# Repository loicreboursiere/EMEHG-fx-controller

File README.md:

# EMEHG-fx-controller

This repository gathers all elements needed to build and run EMEHG-fx-controller.
This device contains a 4x7 rotary encoders matrix with push option.
The encoders matrix aims at controlling hexaphonic audio effects parameters through MIDI CC messages.
 As it sends out MIDI commands, this controller can be use for any kind of control operation.
 This project is a part of the developments made for Loïc Reboursière Phd Thesis : 
    "Organology, genealogy and practice of hexaphonic guitar : from independent string effects to instrumental control of other sounds." 
 
This version is based on a Teensy 3.2. The PCB has been moved to a separate box and Oled display and master rotary encoders has been added.
 
 The folder is organized as follows : 
 ```
 EMEHG-fx-controller.
 └───cad_drawings
 └───code
 └───datasheet
 └───fritzing
 └───img
 └───pcb
 └───Pd
 ```
- cad_drawings : contains a document with drawings of rotaries with the correct spacing.
- code : contains the code to be uploaded on the microcontroller. Depending on the version you're using, the structure of this folder can change (Arduino sketch or Platform IO (through VS) code).
- datasheet : datasheets of used components.
- img : pictures of the different versions of the controller.
- pcb : files for producing pcb
- Pd : test pd patches that receive data from the controller and display them.

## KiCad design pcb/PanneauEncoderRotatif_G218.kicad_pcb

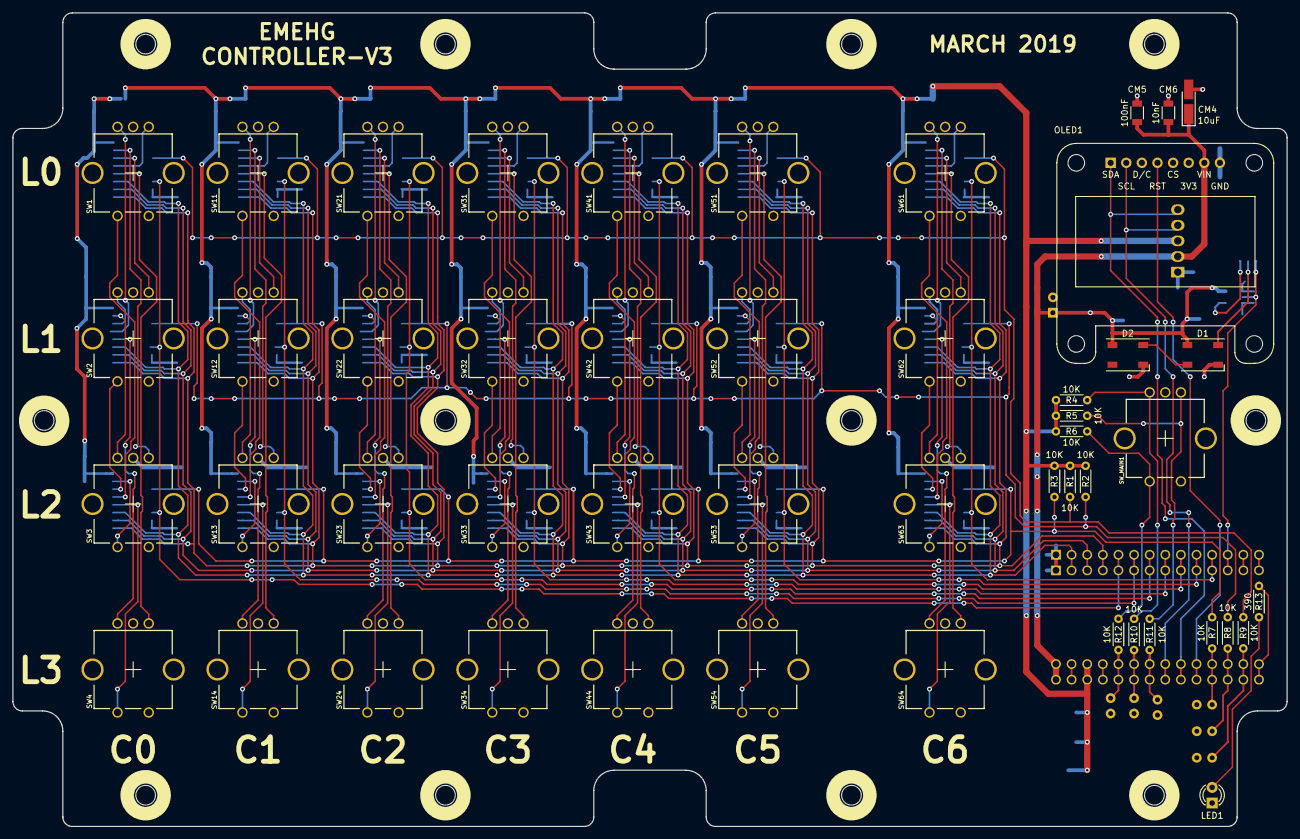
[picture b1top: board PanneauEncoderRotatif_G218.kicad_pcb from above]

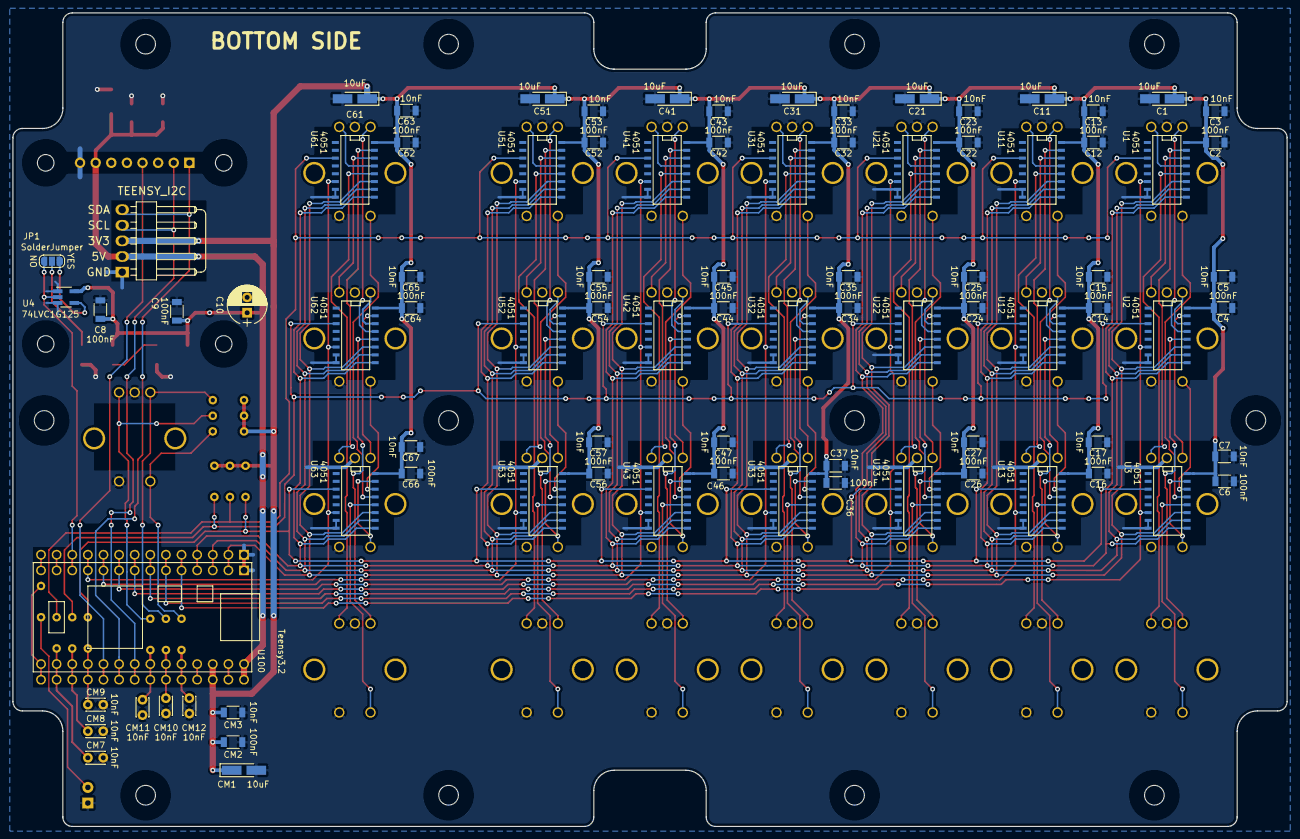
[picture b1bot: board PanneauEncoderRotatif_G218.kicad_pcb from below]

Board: 2 copper layers, 207.3 x 132.3 mm, 135 parts (86 on the bottom side), 118 nets.

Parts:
C1, C11, C21, C31, C41, C51, C61: 10uF; CP_Tantalum_Case-A_EIA-3216-18_Hand
C2, C4, C6, C8, C9, C12, C14, C16, C22, C24, C26, C32, C34, C36, C42, C44, C46, C52, C54, C56, C62, C64, C66: 100nF; C_1206
C3, C5, C7, C13, C15, C17, C23, C25, C27, C33, C35, C37, C43, C45, C47, C53, C55, C57, C63, C65, C67: 10nF; C_1206
C10: 100u; CP_Radial_D6.3mm_P2.50mm
CM1, CM4: 10uF; CP_Tantalum_Case-A_EIA-3216-18_Hand
CM2, CM5: 100nF; C_1206
CM3, CM6: 10nF; C_1206
CM7, CM8, CM9, CM10, CM11, CM12: 10nF; C_Disc_D3.0mm_W2.0mm_P2.50mm
D1, D2: WS2812B; LED_WS2812B-PLCC4
JP1: SolderJumper; SolderJumper-3_P1.3mm_Open_RoundedPad1.0x1.5mm_NumberLabels
LED1: LED; LED_D3.0mm
OLED1: Conn_01x08; Adafruit_SSD1306
R1, R2, R3, R4, R5, R6, R7, R8, R9, R10, R11, R12: 10K; R_Axial_DIN0204_L3.6mm_D1.6mm_P5.08mm_Horizontal
R13: 390; R_Axial_DIN0204_L3.6mm_D1.6mm_P5.08mm_Horizontal
SW1, SW2, SW3, SW4, SW11, SW12, SW13, SW14, SW21, SW22, SW23, SW24, SW31, SW32, SW33, SW34, SW41, SW42, SW43, SW44, SW51, SW52, SW53, SW54, SW61, SW62, SW63, SW64: ENCODER-SWITCH; ROTARY_ENC_PLAIN
SW_MAIN1: ENCODER-SWITCH; ROTARY_ENC_PLAIN
TEENSY_I2C: Conn_01x05; Molex_KK-254_1x05_P2.54mm_Horizontal
U1, U2, U3, U11, U12, U13, U21, U22, U23, U31, U32, U33, U41, U42, U43, U51, U52, U53, U61, U62, U63: 4051; SO-16-N
U4: 74LVC1G125; SOT-23-5_HandSoldering
U100: Teensy3.2; Teensy30_31_32_LC

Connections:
3V3: C1.1, C2.2, C3.2, C4.2, C5.2, C6.2, C7.2, C11.1, C12.2, C13.2, C14.2, C15.2, C16.2, C17.2, C21.1, C22.2, C23.2, C24.2, C25.2, C26.2, C27.2, C31.1, C32.2, C33.2, C34.2, C35.2, C36.2, C37.2, C41.1, C42.2, C43.2, C44.2, C45.2, C46.2, C47.2, C51.1, C52.2, C53.2, C54.2, C55.2, C56.2, C57.2, C61.1, C62.2, C63.2, C64.2, C65.2, C66.2, C67.2, CM1.1, CM2.2, CM3.2, R1.1, R2.1, R3.1, R4.1, R5.1, R6.1, TEENSY_I2C.3, U1.16, U2.16, U3.16, U11.16, U12.16, U13.16, U21.16, U22.16, U23.16, U31.16, U32.16, U33.16, U41.16, U42.16, U43.16, U51.16, U52.16, U53.16, U61.16, U62.16, U63.16, U100.31
+5V: C8.2, C9.2, C10.1, CM4.1, CM5.2, CM6.2, D1.1, D2.1, OLED1.7, TEENSY_I2C.2, U100.33
BP: R3.2, R7.1, U3.3, U13.3, U23.3, U33.3, U43.3, U53.3, U63.3
BP_F: CM9.1, R7.2, U100.23
CH_A: R1.2, R9.1, U1.3, U11.3, U21.3, U31.3, U41.3, U51.3, U61.3
CH_A_F: CM7.1, R9.2, U100.21
CH_B: R2.2, R8.1, U2.3, U12.3, U22.3, U32.3, U42.3, U52.3, U62.3
CH_B_F: CM8.1, R8.2, U100.22
Enable_Column0: U1.6, U2.6, U3.6, U100.5
Enable_Column1: U11.6, U12.6, U13.6, U100.6
Enable_Column2: U21.6, U22.6, U23.6, U100.7
Enable_Column3: U31.6, U32.6, U33.6, U100.8
Enable_Column4: U41.6, U42.6, U43.6, U100.9
Enable_Column5: U51.6, U52.6, U53.6, U100.10
Enable_Column6: U61.6, U62.6, U63.6, U100.11
GND: C1.2, C2.1, C3.1, C4.1, C5.1, C6.1, C7.1, C8.1, C9.1, C10.2, C11.2, C12.1, C13.1, C14.1, C15.1, C16.1, C17.1, C21.2, C22.1, C23.1, C24.1, C25.1, C26.1, C27.1, C31.2, C32.1, C33.1, C34.1, C35.1, C36.1, C37.1, C41.2, C42.1, C43.1, C44.1, C45.1, C46.1, C47.1, C51.2, C52.1, C53.1, C54.1, C55.1, C56.1, C57.1, C61.2, C62.1, C63.1, C64.1, C65.1, C66.1, C67.1, CM1.2, CM2.1, CM3.1, CM4.2, CM5.1, CM6.1, CM7.2, CM8.2, CM9.2, CM10.2, CM11.2, CM12.2, D1.3, D2.3, LED1.1, OLED1.8, SW1.C, SW1.SW-, SW2.C, SW2.SW-, SW3.C, SW3.SW-, SW4.C, SW4.SW-, SW11.C, SW11.SW-, SW12.C, SW12.SW-, SW13.C, SW13.SW-, SW14.C, SW14.SW-, SW21.C, SW21.SW-, SW22.C, SW22.SW-, SW23.C, SW23.SW-, SW24.C, SW24.SW-, SW31.C, SW31.SW-, SW32.C, SW32.SW-, SW33.C, SW33.SW-, SW34.C, SW34.SW-, SW41.C, SW41.SW-, SW42.C, SW42.SW-, SW43.C, SW43.SW-, SW44.C, SW44.SW-, SW51.C, SW51.SW-, SW52.C, SW52.SW-, SW53.C, SW53.SW-, SW54.C, SW54.SW-, SW61.C, SW61.SW-, SW62.C, SW62.SW-, SW63.C, SW63.SW-, SW64.C, SW64.SW-, SW_MAIN1.C, SW_MAIN1.SW-, TEENSY_I2C.1, U1.7, U1.8, U2.7, U2.8, U3.7, U3.8, U4.1, U4.3, U11.7, U11.8, U12.7, U12.8, U13.7, U13.8, U21.7, U21.8, U22.7, U22.8, U23.7, U23.8, U31.7, U31.8, U32.7, U32.8, U33.7, U33.8, U41.7, U41.8, U42.7, U42.8, U43.7, U43.8, U51.7, U51.8, U52.7, U52.8, U53.7, U53.8, U61.7, U61.8, U62.7, U62.8, U63.7, U63.8, U100.1
LCD_RST: OLED1.4, U100.24
NEOPIXEL_IN: D1.4, JP1.2
NEOPIXEL_IN_3V3: JP1.1, U4.2
NEOPIXEL_IN_5V: JP1.3, U4.4
unnamed: D1.2, D2.4
unnamed: LED1.2, R13.2
SCL: OLED1.2, TEENSY_I2C.4, U100.26
SDA: OLED1.1, TEENSY_I2C.5, U100.25
SW01_BP: SW1.SW+, U3.13
SW01_CH_A: SW1.A, U1.13
SW01_CH_B: SW1.B, U2.13
SW02_BP: SW2.SW+, U3.14
SW02_CH_A: SW2.A, U1.14
SW02_CH_B: SW2.B, U2.14
SW03_BP: SW3.SW+, U3.15
SW03_CH_A: SW3.A, U1.15
SW03_CH_B: SW3.B, U2.15
SW04_BP: SW4.SW+, U3.12
SW04_CH_A: SW4.A, U1.12
SW04_CH_B: SW4.B, U2.12
SW11_BP: SW11.SW+, U13.13
SW11_CH_A: SW11.A, U11.13
SW11_CH_B: SW11.B, U12.13
SW12_BP: SW12.SW+, U13.14
SW12_CH_A: SW12.A, U11.14
SW12_CH_B: SW12.B, U12.14
SW13_BP: SW13.SW+, U13.15
SW13_CH_A: SW13.A, U11.15
SW13_CH_B: SW13.B, U12.15
SW14_BP: SW14.SW+, U13.12
SW14_CH_A: SW14.A, U11.12
SW14_CH_B: SW14.B, U12.12
SW21_BP: SW21.SW+, U23.13
SW21_CH_A: SW21.A, U21.13
SW21_CH_B: SW21.B, U22.13
SW22_BP: SW22.SW+, U23.14
SW22_CH_A: SW22.A, U21.14
SW22_CH_B: SW22.B, U22.14
SW23_BP: SW23.SW+, U23.15
SW23_CH_A: SW23.A, U21.15
SW23_CH_B: SW23.B, U22.15
SW24_BP: SW24.SW+, U23.12
SW24_CH_A: SW24.A, U21.12
SW24_CH_B: SW24.B, U22.12
SW31_BP: SW31.SW+, U33.13
SW31_CH_A: SW31.A, U31.13
SW31_CH_B: SW31.B, U32.13
SW32_BP: SW32.SW+, U33.14
SW32_CH_A: SW32.A, U31.14
SW32_CH_B: SW32.B, U32.14
SW33_BP: SW33.SW+, U33.15
SW33_CH_A: SW33.A, U31.15
SW33_CH_B: SW33.B, U32.15
SW34_BP: SW34.SW+, U33.12
SW34_CH_A: SW34.A, U31.12
SW34_CH_B: SW34.B, U32.12
SW41_BP: SW41.SW+, U43.13
SW41_CH_A: SW41.A, U41.13
SW41_CH_B: SW41.B, U42.13
SW42_BP: SW42.SW+, U43.14
SW42_CH_A: SW42.A, U41.14
SW42_CH_B: SW42.B, U42.14
SW43_BP: SW43.SW+, U43.15
SW43_CH_A: SW43.A, U41.15
SW43_CH_B: SW43.B, U42.15
SW44_BP: SW44.SW+, U43.12
SW44_CH_A: SW44.A, U41.12
SW44_CH_B: SW44.B, U42.12
SW51_BP: SW51.SW+, U53.13
SW51_CH_A: SW51.A, U51.13
SW51_CH_B: SW51.B, U52.13
SW52_BP: SW52.SW+, U53.14
SW52_CH_A: SW52.A, U51.14
SW52_CH_B: SW52.B, U52.14
SW53_BP: SW53.SW+, U53.15
SW53_CH_A: SW53.A, U51.15
SW53_CH_B: SW53.B, U52.15
SW54_BP: SW54.SW+, U53.12
SW54_CH_A: SW54.A, U51.12
SW54_CH_B: SW54.B, U52.12
SW61_BP: SW61.SW+, U63.13
SW61_CH_A: SW61.A, U61.13
SW61_CH_B: SW61.B, U62.13
SW62_BP: SW62.SW+, U63.14
SW62_CH_A: SW62.A, U61.14
SW62_CH_B: SW62.B, U62.14
SW63_BP: SW63.SW+, U63.15
SW63_CH_A: SW63.A, U61.15
SW63_CH_B: SW63.B, U62.15
SW64_BP: SW64.SW+, U63.12
SW64_CH_A: SW64.A, U61.12
SW64_CH_B: SW64.B, U62.12
Select_A: U1.11, U2.11, U3.11, U11.11, U12.11, U13.11, U21.11, U22.11, U23.11, U31.11, U32.11, U33.11, U41.11, U42.11, U43.11, U51.11, U52.11, U53.11, U61.11, U62.11, U63.11, U100.2
Select_B: U1.10, U2.10, U3.10, U11.10, U12.10, U13.10, U21.10, U22.10, U23.10, U31.10, U32.10, U33.10, U41.10, U42.10, U43.10, U51.10, U52.10, U53.10, U61.10, U62.10, U63.10, U100.3
Select_C: U1.9, U2.9, U3.9, U11.9, U12.9, U13.9, U21.9, U22.9, U23.9, U31.9, U32.9, U33.9, U41.9, U42.9, U43.9, U51.9, U52.9, U53.9, U61.9, U62.9, U63.9, U100.4
TEENSY_LED: R13.1, U100.20
UI_BP: R6.2, R12.1, SW_MAIN1.SW+
UI_BP_F: CM12.1, R12.2, U100.29
UI_CH_A: R5.2, R11.1, SW_MAIN1.A
UI_CH_A_F: CM11.1, R11.2, U100.27
UI_CH_B: R4.2, R10.1, SW_MAIN1.B
UI_CH_B_F: CM10.1, R10.2, U100.28

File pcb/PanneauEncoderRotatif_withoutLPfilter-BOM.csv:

"Component Count:,""129"""
"Ref,""Qnty"",""Value"",""Cmp name"",""Footprint"",""Description"",""Vendor"""
"C1, C11, C21, C31, C41, C51, C61, ,""7"",""10uF"",""CP-Device"",""Capacitors_Tantalum_SMD:CP_Tantalum_Case-A_EIA-3216-18_Hand"","""","""""
"C2, C4, C6, C8, C9, C12, C14, C16, C22, C24, C26, C32, C34, C36, C42, C44, C46, C52, C54, C56, C62, C64, C66, ,""23"",""100nF"",""C-Device"",""Capacitors_SMD:C_1206"","""","""""
"C3, C5, C7, C13, C15, C17, C23, C25, C27, C33, C35, C37, C43, C45, C47, C53, C55, C57, C63, C65, C67, ,""21"",""10nF"",""C-Device"",""Capacitors_SMD:C_1206"","""","""""
"C10, ,""1"",""100u"",""CP"",""Capacitors_THT:CP_Radial_D6.3mm_P2.50mm"",""Polarized capacitor"","""""
"CM1, CM4, ,""2"",""10uF"",""CP-Device"",""Capacitors_Tantalum_SMD:CP_Tantalum_Case-A_EIA-3216-18_Hand"","""","""""
"CM2, CM5, ,""2"",""100nF"",""C-Device"",""Capacitors_SMD:C_1206"","""","""""
"CM3, CM6, ,""2"",""10nF"",""C-Device"",""Capacitors_SMD:C_1206"","""","""""
"CM10, CM11, CM12, ,""3"",""10nF"",""C-Device"",""Capacitors_THT:C_Disc_D3.0mm_W2.0mm_P2.50mm"","""","""""
"D1, D2, ,""2"",""WS2812B"",""WS2812B"",""LEDs:LED_WS2812B-PLCC4"",""RGB LED with integrated controller"","""""
"JP1, ,""1"",""SolderJumper"",""SolderJumper_3_Open"",""Jumper:SolderJumper-3_P1.3mm_Open_RoundedPad1.0x1.5mm_NumberLabels"",""Solder Jumper, 3-pole, open"","""""
"LED1, ,""1"",""LED"",""LED"","""",""Light emitting diode"","""""
"OLED1, ,""1"",""Conn_01x08"",""Conn_01x08"",""Display:Adafruit_SSD1306"",""Generic connector, single row, 01x08, script generated (kicad-library-utils/schlib/autogen/connector/)"","""""
"R1, R2, R3, R4, R5, R6, R10, R11, R12, ,""9"",""10K"",""R_US"",""Resistors_THT:R_Axial_DIN0204_L3.6mm_D1.6mm_P5.08mm_Horizontal"",""Resistor, US symbol"","""""
"R13, ,""1"",""390"",""R_US"",""Resistors_THT:R_Axial_DIN0204_L3.6mm_D1.6mm_P5.08mm_Horizontal"",""Resistor, US symbol"","""""
"SW1, SW2, SW3, SW4, SW11, SW12, SW13, SW14, SW21, SW22, SW23, SW24, SW31, SW32, SW33, SW34, SW41, SW42, SW43, SW44, SW51, SW52, SW53, SW54, SW61, SW62, SW63, SW64, ,""28"",""ENCODER-SWITCH"",""ENCODER-SWITCH-SparkFun-Switches"",""SparkFun_Switches:ROTARY_ENC_PLAIN"","""","""""
"SW_MAIN1, ,""1"",""ENCODER-SWITCH"",""ENCODER-SWITCH-SparkFun-Switches"",""SparkFun_Switches:ROTARY_ENC_PLAIN"","""","""""
"TEENSY_I2C_1, ,""1"",""Conn_01x05"",""Conn_01x05"",""MolexConnector:Molex_KK-254_1x05_P2.54mm_Horizontal"",""Generic connector, single row, 01x05, script generated (kicad-library-utils/schlib/autogen/connector/)"","""""
"U1, U2, U3, U11, U12, U13, U21, U22, U23, U31, U32, U33, U41, U42, U43, U51, U52, U53, U61, U62, U63, ,""21"",""4051"",""4051-4xxx"",""SMD_Packages:SO-16-N"","""","""""
"U4, ,""1"",""74LVC1G125"",""74LVC1G125"",""TO_SOT_Packages_SMD:SOT-23-5_HandSoldering"",""Single Buffer Gate Tri-State, Low-Voltage CMOS"","""""
"U100, ,""1"",""Teensy3.2"",""Teensy3.2-teensy"",""teensy:Teensy30_31_32_LC"","""","""""

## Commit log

2020-06-16 Add files via upload
    One file throught upload to test submodule in emehg repo
2021-07-24 EMEHG-fx-controller-v1
2021-07-24 v2 first commit on branch
2021-07-24 Add of images (not pcb files yet) of pcb, corresponding sources and gitignore
2021-07-24 first commit on v3 branch, missing pcb files
2021-07-30 Addition of EMEHG-fx-controller-v2 picture
2021-08-02 Remove of PCB_Colonne files
2021-08-02 Add of pcb subfolder
2021-08-02 Add of code from v1 to make folder complete
2021-08-03 v3 updated with pcb files
2021-08-03 v3 updated with pcb files - with actual files
2021-08-03 Adaptation of pcb folder structure
